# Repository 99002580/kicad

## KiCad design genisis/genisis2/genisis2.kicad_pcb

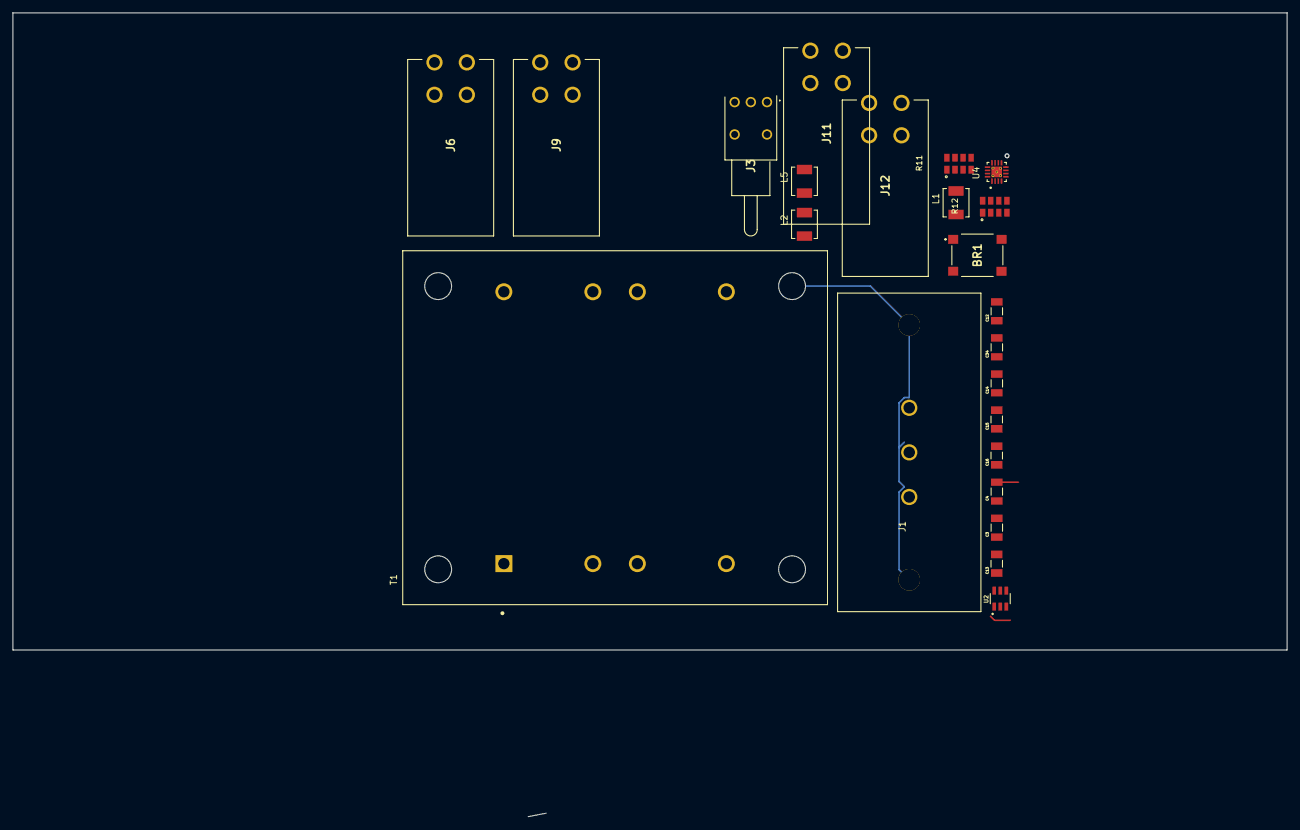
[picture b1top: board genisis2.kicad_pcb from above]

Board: 4 copper layers, 200.0 x 100.0 mm, 23 parts (0 on the bottom side), 15 nets.

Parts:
BR1: DBF310-13; DBF31013
C3, C4, C12, C34: C1206C106J3RACAUTO; CAPC3216X110N
C13, C15, C16: CL31A226KAHNNNE; CAPC3216X180N
C14: C1206C332F3HAC7800; CAPC3216X100N
J1: IEC-A-4
J3: 200MSP1T1B2M6QE
J6, J9, J11, J12: CT3151SP-2; CT3151SP2
L1, L2, L5: SRP4020TA-2R2M; IND_SRP4020TA-2R2M
R11: RK73H2ATTD1502F; RESCAV127P508X200X70-8N
R12: RK73H2ATTD4301F; RESCAV127P508X200X70-8N
T1: VPP12-2400; XFMR_VPP12-2400
U2: TPS562201DDCR; SOT95P280X110-6N
U4: TPS62140RGTT; QFN50P300X300X100-17N

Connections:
+0.8V-3.3V: C16.1, C34.1, J6.1, J6.2, J6.3, J6.4
+1.2V: J9.1, J9.2, J9.3, J9.4, U4.14
+1.8V: C13.1, J11.1, J11.2, J11.3, J11.4, L2.2
+3.3V: J12.1, J12.2, J12.3, J12.4, L5.2
+5V: C15.1, L1.2, R11.1, R12.1
+12V: C3.1, C4.1, C12.1, J3.2, U2.3, U2.5, U4.10, U4.11, U4.12, U4.13
GND: BR1.3, C3.2, C4.2, C12.2, C13.2, C14.2, C15.2, C16.2, C34.2, U2.1, U4.6, U4.7, U4.8, U4.15, U4.16, U4.17
unnamed: BR1.1, J3.3
unnamed: BR1.2, T1.12
unnamed: BR1.4, T1.7
unnamed: J1.1, T1.6
unnamed: J1.3, T1.1
unnamed: U4.1, U4.2, U4.3
unnamed: T1.3, T1.4
unnamed: T1.9, T1.10

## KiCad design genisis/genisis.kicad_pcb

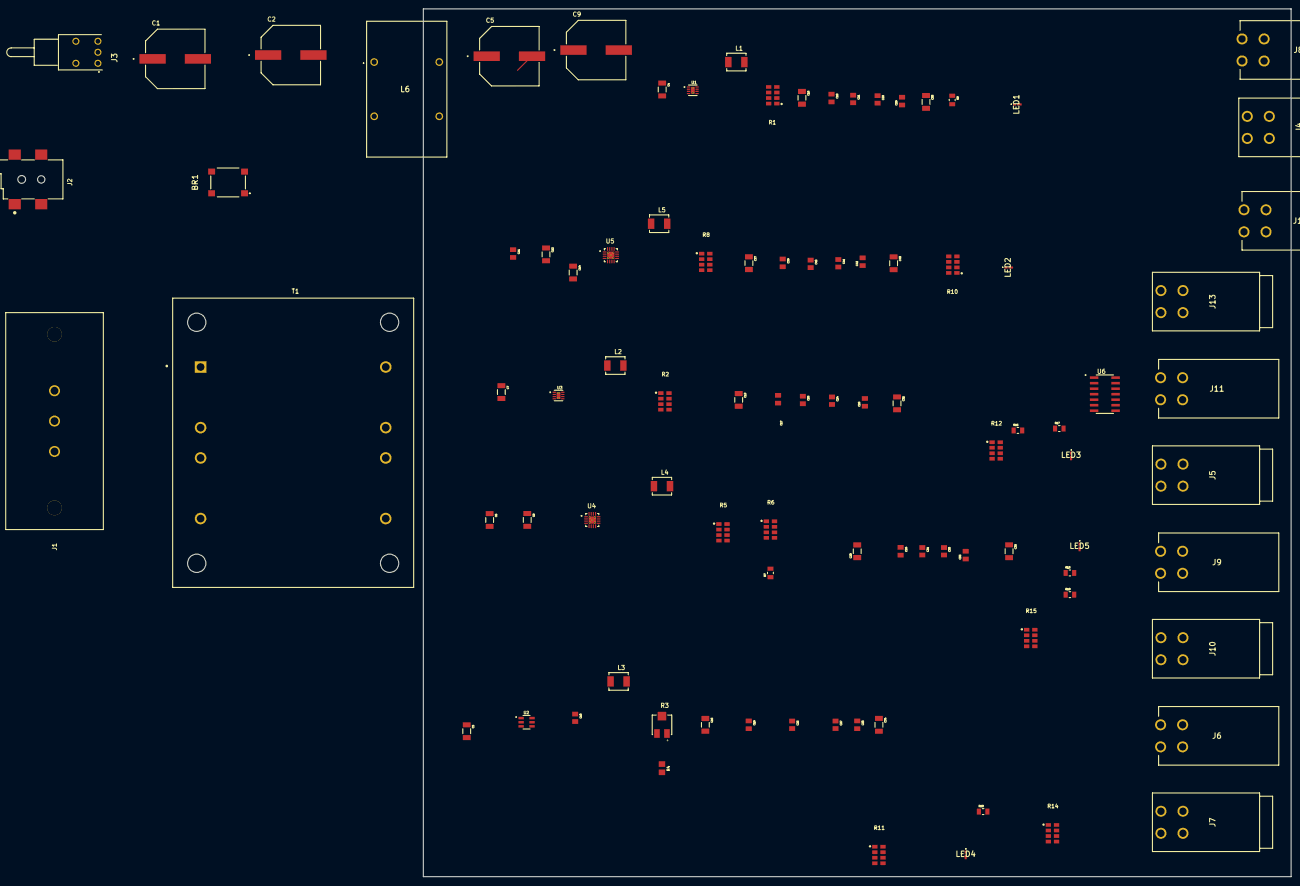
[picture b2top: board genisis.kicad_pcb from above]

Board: 4 copper layers, 200.0 x 200.0 mm, 94 parts (0 on the bottom side), 46 nets.

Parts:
BR1: DBF310-13; DBF31013
C1, C2, C5, C9: EEE-FK1E102AQ; CAPAE1350X1400N
C3, C4, C6, C7, C12, C32, C33, C34, C38, C43: C1206C106J3RACAUTO; CAPC3216X110N
C8, C14: C1206C332F3HAC7800; CAPC3216X100N
C10, C20, C21, C22, C31, C40: CL21B104KACNNNC; CAPC2012X135N
C11, C17, C18, C19, C26, C39: C0805C103F3GACTU; CAPC2012X140N
C13, C15, C16, C23, C37: CL31A226KAHNNNE; CAPC3216X180N
C24, C25, C27, C35, C41: CL21A105KACLNNC; CAPC2012X135N
C28, C29, C30, C36, C42: CL21A475KAQNNNE; CAPC2012X140N
J1: IEC-A-4
J2: PJ-002BH-SMT-TR; CUI_PJ-002BH-SMT-TR
J3: 200MSP1T1B2M6QE
J4, J5, J7, J10, J13: CT3151-0; CT31510
J6, J8, J9, J11, J12: CT3151SP-2; CT3151SP2
L1, L2, L3, L4, L5: SRP4020TA-2R2M; IND_SRP4020TA-2R2M
L6: B82724J8302N040
LED1, LED2, LED3, LED4, LED5: KG_DELLS1.22-JGKH-24; KGDELLS122JGKH24
R1, R2, R5, R8: RK73H2ATTD1003F; RESCAV127P508X200X70-8N
R3: 3314G-1-503E; TRIM_3314J-1-202E
R4: RC0805FR-1310KL; RESC2012X60
R6: SG73S2ATTD7502F; RESCAV127P508X200X70-8N
R7: RK73H2ATTD1503F; RESC2012X60N
R9, R17, R18, R19: RK73H2ATTD1601F; RESC2012X60N
R10: RK73H2ATTD7500F; RESCAV127P508X200X70-8N
R11: RK73H2ATTD1502F; RESCAV127P508X200X70-8N
R12: RK73H2ATTD4301F; RESCAV127P508X200X70-8N
R13: RK73H2ARTTD1802F; RESC2012X60N
R14: RK73H2ATTD2701F; RESCAV127P508X200X70-8N
R15: RK73H2ATTD5101F; RESCAV127P508X200X70-8N
R16: RK73H2ATTD2201F; RESC2012X60N
T1: VPP12-2400; XFMR_VPP12-2400
U1: TPS62163DSGR; SON50P200X200X80-9N
U2: TPS562201DDCR; SOT95P280X110-6N
U3: TPS62161DSGR; SON50P200X200X80-9N
U4: TPS62140RGTT; QFN50P300X300X100-17N
U5: TPS62142RGTR; QFN50P300X300X100-17N
U6: LM324AMX_NOPB; SOIC127P600X175-14N

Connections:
+5V: C15.1, C18.1, C21.1, C25.1, C29.2, C33.1, J8.1, J8.2, J8.3, J8.4, L1.2, R1.1, R9.1, R11.1, R12.1, R13.1, U1.6, U6.4
+12V: C3.1, C4.1, C6.1, C7.1, C11.1, C12.1, J3.2, U1.2, U1.3, U2.3, U2.5, U3.2, U3.3, U4.10, U4.11, U4.12, U4.13, U5.10, U5.11, U5.12, U5.13
GND: BR1.3, C1.1, C2.1, C3.2, C4.2, C5.1, C6.2, C7.2, C8.2, C9.1, C11.2, C12.2, C13.2, C14.2, C15.2, C16.2, C17.2, C18.2, C19.2, C20.2, C21.2, C22.2, C23.1, C24.2, C25.2, C26.2, C27.2, C28.1, C29.1, C30.1, C31.2, C32.2, C33.2, C34.2, C35.2, C36.1, C37.2, C38.2, C39.2, C40.2, C41.2, C42.1, C43.2, J2.2, J2.3, J4.1, J4.2, J4.3, J4.4, J7.1, J7.2, J7.3, J7.4, J10.1, J10.2, J10.3, J10.4, J13.1, J13.2, J13.3, J13.4, LED1.2, LED2.2, LED3.2, LED4.2, LED5.2, R4.2, R7.1, R14.2, R15.2, R16.2, U1.1, U1.4, U1.5, U2.1, U3.1, U3.4, U3.5, U4.6, U4.7, U4.8, U4.15, U4.16, U4.17, U5.5, U5.6, U5.7, U5.8, U5.15, U5.16, U5.17, U6.11
unnamed: BR1.1, C1.2, C2.2, C5.2, C9.2, J3.3, L6.1, L6.2
unnamed: BR1.2, T1.12
unnamed: BR1.4, T1.7
unnamed: L6.3, L6.4
unnamed: C8.1, U4.9
unnamed: C10.1, U2.4
unnamed: C10.2, L3.1, U2.2
unnamed: C13.1, C17.1, C20.1, C24.1, C32.1, L2.2, R2.1, U3.6
unnamed: C14.1, U5.9
unnamed: C16.1, C19.1, C22.1, C27.1, C34.1, L3.2, R3.1
unnamed: C23.2, C26.1, C31.1, C35.1, C38.1, L4.2, R5.1, R6.1, U4.14
unnamed: C37.1, C39.1, C40.1, C41.1, C42.2, C43.1, L5.2, R8.1, R10.1, U5.14
unnamed: J1.1, T1.6
unnamed: J1.3, T1.1
unnamed: J2.1A, J2.1B, J3.1
unnamed: J5.1, J5.2, J5.3, J5.4
unnamed: J6.1, J6.2, J6.3, J6.4
unnamed: J9.1, J9.2, J9.3, J9.4
unnamed: J11.1, J11.2, J11.3, J11.4
unnamed: J12.1, J12.2, J12.3, J12.4
unnamed: L1.1, U1.7
unnamed: L2.1, U3.7
unnamed: L4.1, U4.1, U4.2, U4.3
unnamed: L5.1, U5.1, U5.2, U5.3
unnamed: LED1.1, R9.2
unnamed: LED2.1, R10.2
unnamed: LED3.1, R17.2
unnamed: LED4.1, R18.2
unnamed: LED5.1, R19.2
unnamed: R1.2, U1.8
unnamed: R2.2, U3.8
unnamed: R3.3, R4.1, U2.6
unnamed: R5.2, U4.4
unnamed: R6.2, U4.5
unnamed: R8.2, U5.4
unnamed: R11.2, R14.1, U6.6
unnamed: R12.2, R16.1, U6.9
unnamed: R13.2, R15.1, U6.2
unnamed: R17.1, U6.8
unnamed: R18.1, U6.7
unnamed: R19.1, U6.1
unnamed: T1.3, T1.4
unnamed: T1.9, T1.10
